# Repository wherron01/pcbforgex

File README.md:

# PCBForgeX
```
usage: pcbforgex.py [-h] [-fa FA] [-fs FS] [--slop SLOP]
                    [--cut-depth CUT_DEPTH] [--thickness THICKNESS]
                    [--spacing SPACING] [--output OUTPUT] [--flip]
                    [--no-drill-ends] [--separate] [--no-mirror]

Outputs a 3D printable die for your active KiCAD PCB, rendered with OpenSCAD

options:
  -h, --help            show this help message and exit
  -fa FA                Angle step for rendering curves (default: 5)
  -fs FS                Minimum size for rendering curves (default: 0.1)
  --slop SLOP           Your 3D printer tolerance -- parts printed this
                        distance apart should fit together snugly (default:
                        0.1)
  --cut-depth CUT_DEPTH
                        The distance to press traces down. Ensure that this
                        shears the copper (default: 1)
  --thickness THICKNESS
                        Dielectric thickness, between copper layers (plus cut-
                        depth) (default: 1)
  --spacing SPACING     Space between board layers in export (default: 2)
  --output OUTPUT       Output filename with desired extension for export.
                        Supports everything OpenSCAD does plus scad itself and
                        - for stdout (default: output.stl)
  --flip                Turn mold inside out -- punch on top and die on
                        bottom. Useful for SMT components on the top layer
                        (default: False)
  --no-drill-ends       Don't extend top and bottom layer drills to the layer
                        caps (default: False)
  --separate            Export each layer as its own file (default: False)
  --no-mirror           Don't mirror the board to match KiCAD. You usually
                        never want this (default: False)
```
### To use the generated models:
1. Place copper tape over one half of the first layer,
2. Press the other half of the same layer into it to shear the copper,
3. Separate the two halves,
4. Remove the copper from the negative parts of the layer,
5. Repeat steps 1-4 for each layer,
6. Put the layers back together,
7. Assemble components onto the completed board.

### This method has several advantages over traditional solutions:
1. It can generate as many layers as you want. 50 layer PCB at home? Easy.
2. THT assembly can be solderless, by using the leads to punch through the copper tape.
3. It only uses inexpensive consumables and tools that most hobbyists already have.

### The script works on your active PCB document, so you must have it open in KiCAD.

This is because for some reason KiCAD decided to remove API support for their files. 

They now only support IPC with a running KiCAD process. 

You may also need to enable the KiCAD API in the software. 

### This script generates a single 3D printable STL by default.

It will need to be split into parts in a slicer.

You can also generate individual files, or files of any standard 3D format.

This script also can skip compilation and give you the generated SCAD file directly.

This is intended for tinkerers who wish to tweak the output beyond these parameters.

### This script relies on an external OpenSCAD installation.

If you do not have OpenSCAD, you can still generate scads, but not compile them.

The output, whether internally rendered or not, must have access to pcbforgex.scad.

In turn, pcbforgex.scad must have access to BOSL2, the Belfry OpenSCAD Library.

This is included as a submodule of this repository, which you can clone recursively.

As long as you maintain the directory structure, things should Just Work.

Alternatively, if you already have the library installed, a shallow clone will find it.

### This script also has a single python dependency.

Of course, this is the KiCAD API itself.

It should be installable with pip from requirements.txt.

If your system is externally managed, you can install this in a virtual environment.

Using a venv is probably best practice anyways.

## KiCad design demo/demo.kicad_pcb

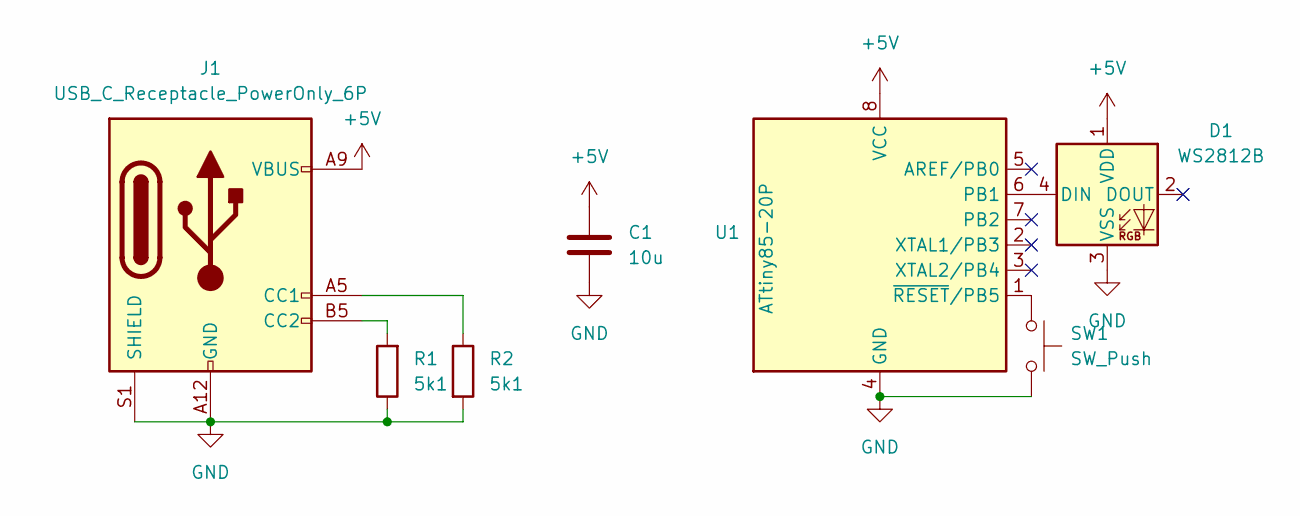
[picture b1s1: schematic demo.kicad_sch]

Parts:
C1: 10u; C_0805_2012Metric_Pad1.18x1.45mm_HandSolder
D1: WS2812B; LED_WS2812B_PLCC4_5.0x5.0mm_P3.2mm
J1: USB_C_Receptacle_PowerOnly_6P; USB_C_Receptacle_GCT_USB4125-xx-x_6P_TopMnt_Horizontal
R1, R2: 5k1; C_0805_2012Metric_Pad1.18x1.45mm_HandSolder
SW1: SW_Push; SW_PUSH_6mm
U1: ATtiny85-20P; DIP-8_W7.62mm

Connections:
+5V: C1.1, D1.1 (VDD), J1.A9 (VBUS), J1.B9 (VBUS), U1.8 (VCC)
GND: C1.2, D1.3 (VSS), J1.A12 (GND), J1.B12 (GND), J1.S1 (SHIELD), R1.1, R2.2, SW1.2, U1.4 (GND)
unnamed: D1.4 (DIN), U1.6 (PB1)
unnamed: J1.A5 (CC1), R2.1
unnamed: J1.B5 (CC2), R1.2
unnamed: SW1.1, U1.1 (~RESET/PB5)

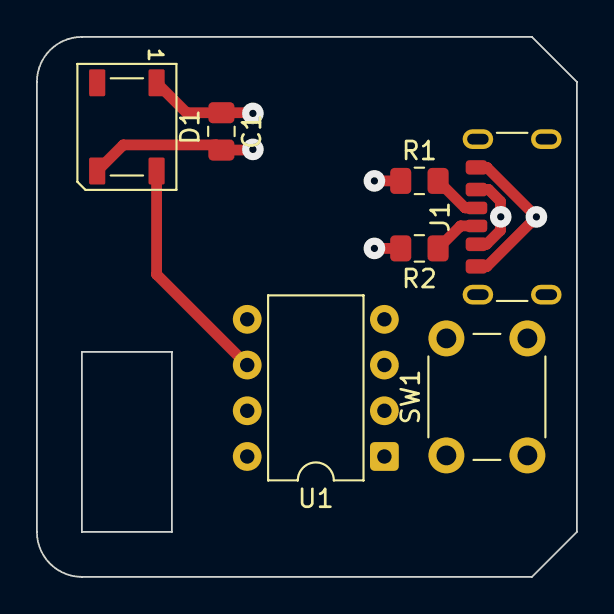
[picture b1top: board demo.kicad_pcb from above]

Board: 4 copper layers, 30.0 x 30.0 mm, 7 parts (0 on the bottom side), 6 nets.

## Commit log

2026-02-23 init
2026-02-24 big things
2026-02-24 structure
2026-02-24 moar structure
2026-02-24 submodules are hard
2026-02-24 submodule
2026-02-25 refactor numero dos -- the modularizing
2026-02-25 updaet documentation
2026-03-06 demo work
2026-03-12 pad hole slop fix, structural drills, and documentation update
